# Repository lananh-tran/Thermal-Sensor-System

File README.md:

# Thermal Sensor System

by Lan-Anh Tran

_Many thanks to Carter Trudeau and Kyle Chen for their help in this project._

## Introduction

We are part of the [Chico Rocketry and Aerospace Club](https://www.instagram.com/chicorocketry/) at California State University, Chico. This is the documentation of one of our electronic modules for our rocket - the Wildcat V, which our team brought to [IREC 2025](https://www.herox.com/IREC2025) (International Rocket Engineering Competition). The purpose of this module is to take measurements of the surrounding ambient temperature and inner surface temperature of the rocket before and during flight for simulation purposes. The components used in this project can be viewed in the [Bill of Materials](https://github.com/lananh-tran/Thermal-Sensor-System/blob/1d724febd7ca4944d8594dc0ccbd3dcf55217213/Thermal%20Sensor%20System%20BOM%202025.xlsx) or shown below:

- [Adafruit MAX31865 PT100 RTD Temperature Sensor Amplifier](https://www.adafruit.com/product/3328)
- [Adafruit MCP9808 I2C Temperature Sensor Breakout Board](https://www.adafruit.com/product/1782)
- [MPU6050 Analog Gyro Sensors and Accelerometer Module](https://www.amazon.com/Gy-521-MPU-6050-MPU6050-Sensors-Accelerometer/dp/B008BOPN40?sr=8-2)
- [HiLetgo Micro SD TF Card Adapter Reader Module](https://www.amazon.com/HiLetgo-Adater-Interface-Conversion-Arduino/dp/B07BJ2P6X6?sr=8-1)
- [Battery Charger Module](https://www.amazon.com/dp/B098989NRZ?amp=&amp=)
- [Samsung 35E 18650 3500mAh 8A - Button Top Battery](https://www.18650batterystore.com/products/samsung-35e-button-top)
- [Arduino Nano Microcontroller](https://www.amazon.com/LAFVIN-Board-ATmega328P-Micro-Controller-Arduino/dp/B07G99NNXL?sr=8-1)
- [Surface Mount RTD PT100 Temperature Sensor](https://evosensors.com/products/p3a-tape-rec-px-1-pfxx-40-stwl?variant=29631284299&country=US&currency=USD&gQT=1)

Link to the KiCad [schematic](https://github.com/lananh-tran/Thermal-Sensor-System/blob/4369b679e1e1e8256428873dc583f430bf157983/Thermal-System.kicad_sch) and [PCB layout](https://github.com/lananh-tran/Thermal-Sensor-System/blob/4369b679e1e1e8256428873dc583f430bf157983/Thermal-System.kicad_pcb) files.

## Design Procedure

Below is the rough design for the sensor system. See [design schematic](https://github.com/lananh-tran/Thermal-Sensor-System/blob/db7faa17b55e4ecaf4507a09ca1c67294a6be1d8/Thermal%20System%20Schematic.pdf) and [PCB layout](https://github.com/lananh-tran/Thermal-Sensor-System/blob/db7faa17b55e4ecaf4507a09ca1c67294a6be1d8/Thermal%20System%20PCB.pdf) for more details.

Except for the RTD sensor, the battery charger module, and the 18650 battery, the rest are mounted on a PCB.

The MCP9808 and the MPU6050 both utilize the I2C communication protocol, while the MAX31865 and the microSD Card Adapter use the SPI protocol. Though we couldn't find a particular reason why there aren't any I2C breakout boards for the MAX31865, we assume the microSD Card Adapter has to use SPI due to its need for speed. This resulted in a communication issue, which will be discussed in the Results section.

I2C devices communicate through two lines - the clock (SCL) and the data line (SDA). An I2C master can be connected to different slaves, as long as their SDA lines are connected and their SCL lines are connected.

SPI devices require more connections, with a clock line (SCK or CLK), Master-In-Slave-Out (MISO or SDO), Master-Out-Slave-In (MOSI or SDI), and a Chip Select line (CS). Multiple SPI slaves can have their CLK, MISO, and MOSI lines connected to the corresponding lines of their master, but each slave has to be connected to a different CS pin on their master.

In order to mitigate the potential wiring errors, we opt to design and fabricate a custom PCB of size 6 x 1.6 in, with a drill hole diameter of 0.1 in. The design is done in KiCad, which is a powerful and free PCB design software. KiCad also allows 3D modelling, which is quite convenient if you want to make sure the electrical design is compatible with the mechanical structure.

## Assembly Process

The assembly process is quite straightforward. After soldering all the components onto the PCB, connect the RTD sensor to the MAX31865 breakout board as shown below, then connect the battery and charger module as demonstrated in the system schematic posted above.

More details about the MAX31865 wiring can be viewed on [Adafruit's official guide](https://learn.adafruit.com/adafruit-max31865-rtd-pt100-amplifier/rtd-wiring-config).

## Results

We chose [OSH Park](https://oshpark.com/) to fabricate our PCB as they are a US-based company, thereby having a lower shipping cost.

Below is the final product before it was sent to IREC 2025 for competition:

A critical issue we have with this module is the design of the microSD Adapter Module, which leads to the SPI bus not getting off the SPI bus. As a result, we initially couldn't implement multiple SPI devices using a single Arduino. To debug, we opted to utilize the logic analyzer function of the ADALM2000 module to observe the behavior of the system.

Results when the SD module is connected:

When the SD module isn't connected:

After a close inspection of the SD module schematic, we suspect that the MISO might be pulled to GND by default by the buffer, leading to the issue with the SPI bus.

We decided to follow a modification suggested on the Arduino Forum (source lost), as shown below.

Our modified SD module works properly when connected to the system along with the MAX31865 amplifier.

## Code

```
#include <SPI.h>
#include <Wire.h>
#include <SD.h>
#include <Adafruit_MPU6050.h>
#include <Adafruit_Sensor.h>
#include <Adafruit_MCP9808.h>
#include <Adafruit_MAX31865.h>

// --- CONFIGURATION ---
int timeStamp = 1;
#define SD_CS 4
//SdFat SD;
File dataLog;

float acceleration;
Adafruit_MPU6050 mpu;

float ambient;
Adafruit_MCP9808 ambientTemp = Adafruit_MCP9808();

#define RREF 430.0 // Rref resistor for PT100
#define RNOMINAL 100.0 // Nominal resistance for PT100
#define RTD_CS 10
#define MOSI 11
#define MISO 12
#define CLK 13
float surface;
Adafruit_MAX31865 surfaceTemp = Adafruit_MAX31865(RTD_CS);

void setup() {
  // set serial monitor baud rate
  Serial.begin(9600);
  while(!Serial) {;}

  // MCP9808 initialization
  MCP_init();

  // MPU6050 initialization
  MPU_init();

  // SD card initialization
  SD_init();

  // MAX31865 initialization
  pinMode(RTD_CS, OUTPUT);
  digitalWrite(RTD_CS, HIGH);
  surfaceTemp.begin(MAX31865_3WIRE);
  delay(1000);

  // SPI communication setup
  SPI.begin();

  Serial.println("Begin testing:");
}

void loop() {
  // --- MCP9808 Sampling ---
  MCP_sample();

  // testing
  Serial.print("Ambient temp: "); 
  Serial.print(ambient, 3);
  Serial.println("*C");

  // --- MAX31865 Sampling ---
  MAX_sample();

  // testing
  Serial.print("Surface temp: "); 
  Serial.print(surface, 3);
  Serial.println("*C");

  // --- MPU6050 Sampling ---
  MPU_sample();

  // testing
  Serial.print("Acceleration: "); 
  Serial.print(acceleration, 3);
  Serial.println("m/s^2");

  // --- SD card reader ---
  SD_write();

  delay(1000); // take readings every 1s
}

void MCP_init(void) {
  //  A2 A1 A0 address
  //  0  0  0   0x18  this is the default address
  //  0  0  1   0x19
  //  0  1  0   0x1A
  //  0  1  1   0x1B
  //  1  0  0   0x1C
  //  1  0  1   0x1D
  //  1  1  0   0x1E
  //  1  1  1   0x1F
  if(!ambientTemp.begin(0x18)) {
	  Serial.println("Unable to connect to the MCP9808!");
	  Serial.println("Check your connections and verify the address is correct.");
	  while (1);
  }

  // Mode Resolution SampleTime
  //  0    0.5°C       30 ms
  //  1    0.25°C      65 ms
  //  2    0.125°C     130 ms
  //  3    0.0625°C    250 ms
  ambientTemp.setResolution(3);
  //Serial.println("MCP9808 initialized!");
  delay(1000); // Give sensor time to stabilize
}

void MPU_init(void) {
  if (!mpu.begin()) {
    Serial.println("Failed to find MPU6050 chip");
    while (1);
  }

  mpu.setAccelerometerRange(MPU6050_RANGE_16_G);
  mpu.setGyroRange(MPU6050_RANGE_500_DEG);
  mpu.setFilterBandwidth(MPU6050_BAND_21_HZ);

  delay(1000); // Give sensor time to stabilize
}

void SD_init(void) {
  pinMode(SD_CS, OUTPUT);
  digitalWrite(SD_CS, HIGH);
  //Serial.println("Initializing SD card...");
  if(!SD.begin(SD_CS)) {
    Serial.println("SD card initialization failed!");
    //while(1) {;}
  }
  //Serial.println("Card initialized!");

  dataLog = SD.open("DATALOG.csv", FILE_WRITE);
  if(!dataLog) {
    Serial.println("Failed to write!");
    //while(1) {;}
  }
  dataLog.println("no.,ambientTemp(C),surfaceTemp(C),acceleration(m/s^2)");
}

void MCP_sample(void) {
  ambientTemp.wake();
  delay(200);
  ambient = ambientTemp.readTempC();
  ambientTemp.shutdown_wake(1);
  delay(200);
}

void SD_write(void) {
  digitalWrite(RTD_CS, HIGH);
  digitalWrite(SD_CS, LOW);
  
  if(dataLog) {
    dataLog.print(timeStamp);
    dataLog.print(",");
    dataLog.print(ambient, 3);
    dataLog.print(",");
    dataLog.print(surface, 3);
    dataLog.print(",");
    dataLog.println(acceleration, 3);
    
    dataLog.flush();
    delay(200);
  }

  digitalWrite(SD_CS, HIGH);
  timeStamp++;
  Serial.println("Writing done");
}

void MAX_sample(void) {
  digitalWrite(SD_CS, HIGH);
  digitalWrite(RTD_CS, LOW);
  surface = surfaceTemp.temperature(RNOMINAL, RREF);
  delay(200);
  digitalWrite(RTD_CS, HIGH);
}

void MPU_sample(void) {
  // Get new sensor events with the readings
  sensors_event_t a, g, temp;
  mpu.getEvent(&a, &g, &temp);
  acceleration = sqrt(a.acceleration.x * a.acceleration.x +
                        a.acceleration.y * a.acceleration.y +
                        a.acceleration.z * a.acceleration.z) - 9.81; // account for Earth stationary acceleration
}
```

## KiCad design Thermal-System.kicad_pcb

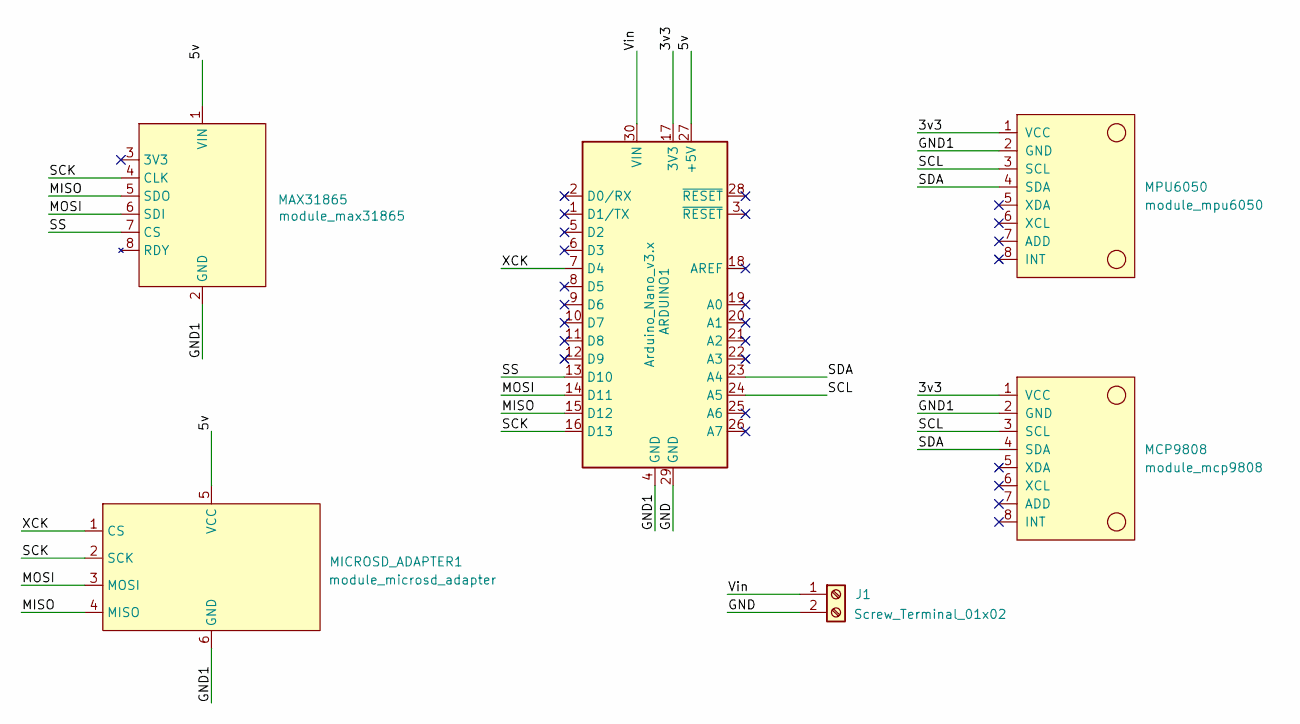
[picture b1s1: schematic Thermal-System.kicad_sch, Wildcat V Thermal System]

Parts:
ARDUINO1: Arduino_Nano_v3.x; Arduino_Nano
J1: Screw_Terminal_01x02; TerminalBlock_MaiXu_MX126-5.0-02P_1x02_P5.00mm
MAX31865: module_max31865
MCP9808: module_mcp9808
MICROSD_ADAPTER1: module_microsd_adapter; module_microsdadapter
MPU6050: module_mpu6050

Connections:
/3v3: ARDUINO1.17 (3V3), MCP9808.1 (VCC), MPU6050.1 (VCC)
/5v: ARDUINO1.27 (+5V), MAX31865.1 (VIN), MICROSD_ADAPTER1.5 (VCC)
/GND: ARDUINO1.29 (GND), J1.2
/GND1: ARDUINO1.4 (GND), MAX31865.2 (GND), MCP9808.2 (GND), MICROSD_ADAPTER1.6 (GND), MPU6050.2 (GND)
/MISO: ARDUINO1.15 (D12), MAX31865.5 (SDO), MICROSD_ADAPTER1.4 (MISO)
/MOSI: ARDUINO1.14 (D11), MAX31865.6 (SDI), MICROSD_ADAPTER1.3 (MOSI)
/SCK: ARDUINO1.16 (D13), MAX31865.4 (CLK), MICROSD_ADAPTER1.2 (SCK)
/SCL: ARDUINO1.24 (A5), MCP9808.3 (SCL), MPU6050.3 (SCL)
/SDA: ARDUINO1.23 (A4), MCP9808.4 (SDA), MPU6050.4 (SDA)
/SS: ARDUINO1.13 (D10), MAX31865.7 (CS)
/Vin: ARDUINO1.30 (VIN), J1.1
/XCK: ARDUINO1.7 (D4), MICROSD_ADAPTER1.1 (CS)

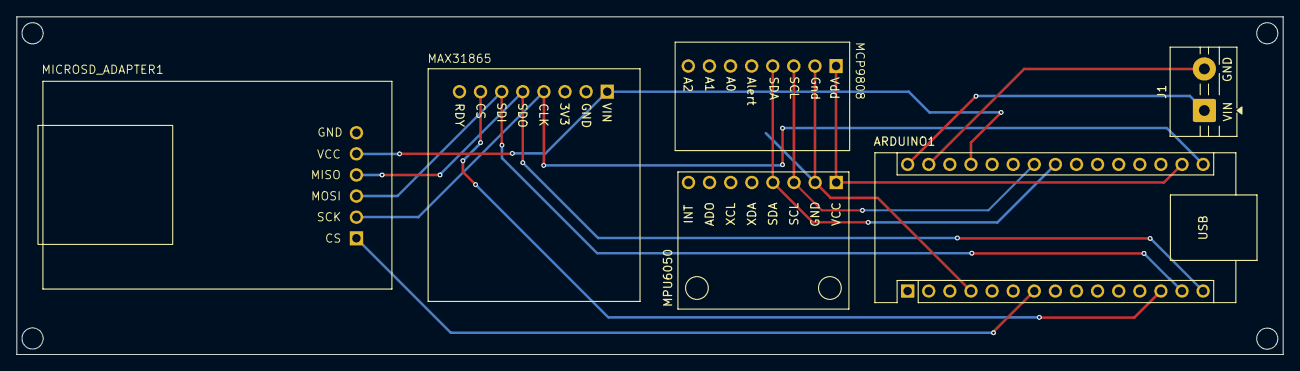
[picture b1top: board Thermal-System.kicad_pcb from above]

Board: 2 copper layers, 152.4 x 40.6 mm, 6 parts (0 on the bottom side), 12 nets.

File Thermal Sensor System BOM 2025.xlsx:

Website | Item | Cost per unit | Quantity | Total | Description | Link |  | Datasheet |  | Dimensions
18650 Battery Store | Samsung 35E 18650 3500mAh 8A - Button Top Battery | 9.99 | 1.0 | 9.99 |  | https://www.18650batterystore.com/products/samsung-35e-button-top
 |  |  | Local total | 9.99
Amazon | Battery Charger Module 6pcs | 9.89 | 1.0 | 9.89 |  | https://www.amazon.com/dp/B098989NRZ?ref_=cm_sw_r_cso_cp_apa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
 | Arduino Nano 3pcs | 15.99 | 1.0 | 15.99 |  | https://www.amazon.com/ELEGOO-Pre-soldered-ATmega-Compatible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 |  | https://www.nitrathor.com/data-sheets/arduino-nano |  | 43.16 mm x 17.76 mm x 2.54 mm
 | MPU-6050 Axis Accelerometer Gyroscope Sensor Module 5pcs | 14.99 | 1.0 | 14.99 |  | https://www.amazon.com/MPU-6050-MPU6050-Accelerometer-Gyrosc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
 | Hiletgo Micro SD Card Reader Module 5pcs | 6.99 | 1.0 | 6.99 |  | https://www.amazon.com/HiLetgo-Adater-Interface-Conversion-A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 |  | http://datalogger.pbworks.com/w/file/fetch/89507207/Datalogg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 |  | ‎76.2 x 58.4 x 10.2 mm
 |  |  | Local total | 47.86
Adafruit | MCP9808 Temperature Sensor Breakout Board | 4.95 | 1.0 | 4.95 |  | https://www.adafruit.com/product/1782 |  | https://cdn-shop.adafruit.com/datasheets/MCP9808.pdf |  | 21mm x 13mm x 2mm / 0.8" x 0.5" x 0.08
 |  |  | Local total | 4.95
Digikey | PT100 RTD Temperature Sensor Amplifier - MAX31865 | 14.95 | 1.0 | 14.95 |  | https://www.digikey.com/en/products/detail/adafruit-industri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 |  | https://www.analog.com/media/en/technical-documentation/data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 |  | 28.0mm x 25.5mm x 3.0mm / 1.1" x 1.0" x 0.1
 |  |  | Local total | 14.95
Evolution | Surface Mount PT100 RTD Temperature Sensor | 45.0 | 1.0 | 45 |  | https://evosensors.com/products/p3a-tape-rec-px-1-pfxx-40-st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 |  | https://cdn.shopify.com/s/files/1/1679/4593/files/P3A-TAPE-R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 |  | 25mm x 19mm (patch)
 |  |  | Local total | 45
 |  |  | Grand total | 112.76

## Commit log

2025-04-11 add parts list and dimensions
2025-04-12 edit datasheets
2025-04-13 add batteries & MPU
2025-04-13 add battery + charger module & replace RTC with MPU
2025-04-13 write report outline
2025-06-24 upload images
2025-06-24 upload schematic
2025-07-02 Rename Screenshot 2025-07-01 221512.png to KiCad Schematic
2025-07-02 Rename KiCad Schematic to KiCad Schematic.png
2025-07-02 upload KiCad files
